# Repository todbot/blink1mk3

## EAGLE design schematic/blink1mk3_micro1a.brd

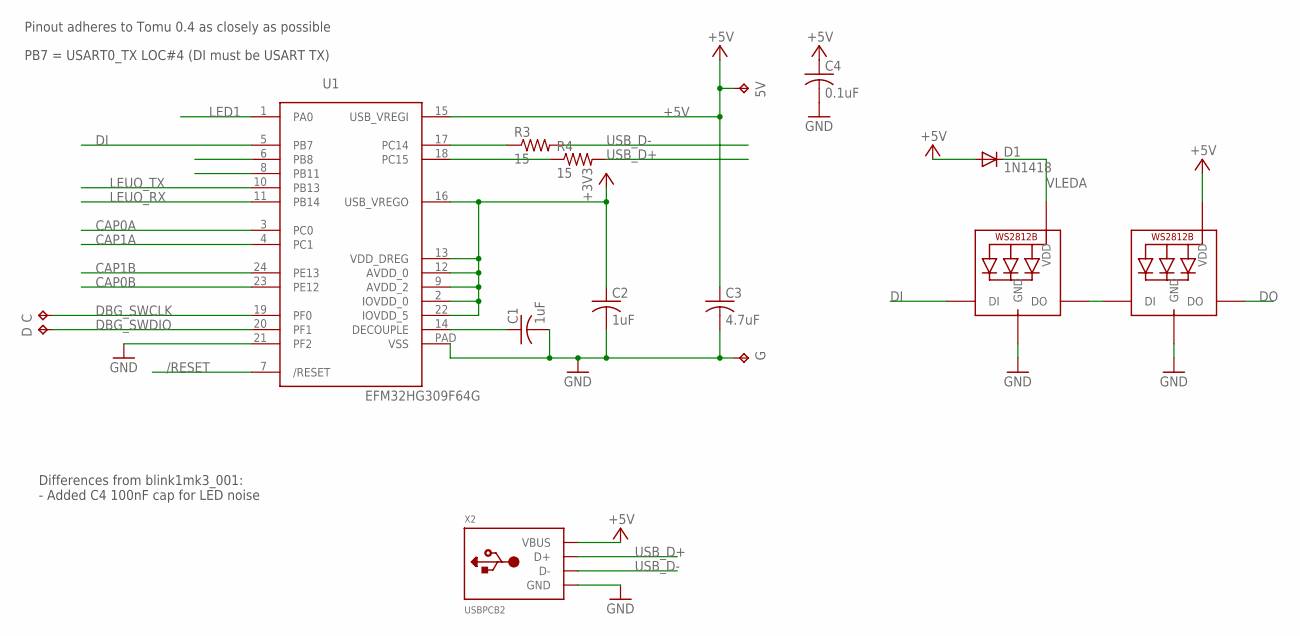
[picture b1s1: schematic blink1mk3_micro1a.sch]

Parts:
5V: TPTP10R; TP10R
C: TPTP10R; TP10R
C1, C2: 1uF; C0402
C3: 4.7uF; C0402
C4: 0.1uF; C0402
D: TPTP10R; TP10R
D1: 1N1418; SOD523
G: TPTP10R; TP10R
LED1, LED2: WS2812B4020SIDE; SK6812-SIDE
R3, R4: 15; R0402
U1: EFM32HG309F64G; QFN24PAD
X2: USBPCB2; USB-A-PCB-2

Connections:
+3V3: C2.1, U1.2 (IOVDD_0), U1.9 (AVDD_2), U1.12 (AVDD_0), U1.13 (VDD_DREG), U1.16 (USB_VREGO), U1.22 (IOVDD_5)
+5V: 5V.TP, C3.1, C4.1, D1.A, LED2.1-VDD (VDD), U1.15 (USB_VREGI), X2.5V (VBUS)
/RESET: U1.7 (/RESET)
CAP0A: U1.3 (PC0)
CAP0B: U1.23 (PE12)
CAP1A: U1.4 (PC1)
CAP1B: U1.24 (PE13)
DBG_SWCLK: C.TP, U1.19 (PF0)
DBG_SWDIO: D.TP, U1.20 (PF1)
DECOUPLE: C1.1, U1.14 (DECOUPLE)
DI: LED1.4-DIN (DI), U1.5 (PB7)
DO: LED2.2-DOUT (DO)
GND: C1.2, C2.2, C3.2, C4.2, G.TP, LED1.3-GND (GND), LED2.3-GND (GND), U1.21 (PF2), U1.PAD (VSS), X2.GND
LED1: U1.1 (PA0)
LEUO_RX: U1.11 (PB14)
LEUO_TX: U1.10 (PB13)
unnamed: LED1.2-DOUT (DO), LED2.4-DIN (DI)
RUSB_D+: R4.1, U1.18 (PC15)
RUSB_D-: R3.1, U1.17 (PC14)
USB_D+: R4.2, X2.USB_P (D+)
USB_D-: R3.2, X2.USB_M (D-)
VLEDA: D1.C, LED1.1-VDD (VDD)

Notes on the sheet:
PB7 = USART0_TX LOC#4 (DI must be USART TX)
Pinout adheres to Tomu 0.4 as closely as possible
Differences from blink1mk3_001: - Added C4 100nF cap for LED noise

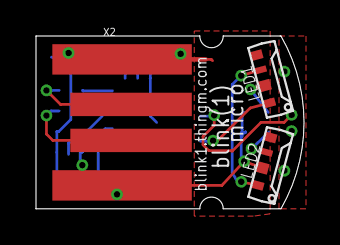
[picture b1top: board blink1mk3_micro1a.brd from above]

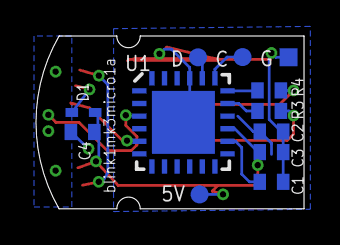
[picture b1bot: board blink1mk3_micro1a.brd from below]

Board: 2 copper layers, 14.9 x 9.6 mm, 15 parts (12 on the bottom side), 13 nets.

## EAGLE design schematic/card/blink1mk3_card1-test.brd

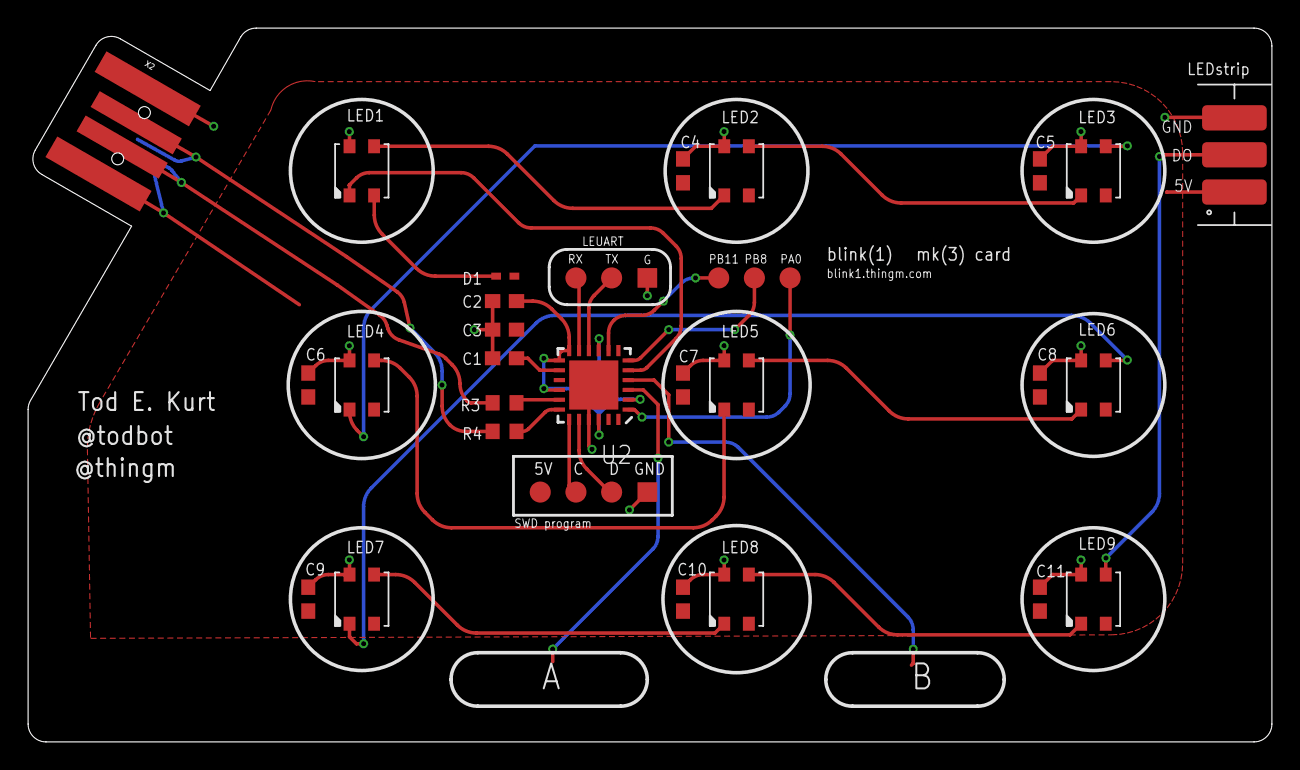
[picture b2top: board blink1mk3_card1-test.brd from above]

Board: 2 copper layers, 88.5 x 50.8 mm, 37 parts (1 on the bottom side), 26 nets.

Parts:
5V: TPTP15R; TP15R
C: TPTP15R; TP15R
C1, C2: 1uF; C0603
C3: 4.7uF; C0603
C4, C5, C6, C7, C8, C9, C10, C11: 0.1uF; C0603
D: TPTP15R; TP15R
D1: 1N1418; SOD523
G: TPTP14SQ; TP14SQ
GND: TPTP14SQ; TP14SQ
J1: NONPOP; USB-B-MICRO-SMD
LED1, LED2, LED3, LED4, LED5, LED6, LED7, LED8, LED9: SK6812MINI; LED3535
PA0: TPTP15R; TP15R
PB8, PB11: TPTP15R; TP15R
R3, R4: 15; R0603
RX: TPTP15R; TP15R
TX: TPTP15R; TP15R
U2: EFM32HG309F64G; QFN24PAD
U$1: LED_STRIP_3P; LEDSTRIP-3P
X2: USBPCB2; USB-A-PCB-2

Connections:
+3V3: C2.1, U2.2, U2.9, U2.12, U2.13, U2.16, U2.22
+5V: 5V.TP, C3.1, C4.1, C5.1, C6.1, C7.1, C8.1, C9.1, C10.1, C11.1, D1.A, J1.VBUS, LED2.2, LED3.2, LED4.2, LED5.2, LED6.2, LED7.2, LED8.2, LED9.2, U2.15, U$1.A, X2.5V
DBG_SWCLK: C.TP, U2.19
DBG_SWDIO: D.TP, U2.20
DECOUPLE: C1.1, U2.14
DI: LED1.1, U2.5
DO: LED9.3, U$1.B
GND: C1.2, C2.2, C3.2, C4.2, C5.2, C6.2, C7.2, C8.2, C9.2, C10.2, C11.2, G.TP, GND.TP, J1.GND, LED1.4, LED2.4, LED3.4, LED4.4, LED5.4, LED6.4, LED7.4, LED8.4, LED9.4, U2.21, U2.PAD, U$1.C, X2.GND
LEUO_RX: RX.TP, U2.11
LEUO_TX: TX.TP, U2.10
unnamed: LED1.3, LED2.1
unnamed: LED7.3, LED8.1
unnamed: LED4.3, LED5.1
unnamed: LED5.3, LED6.1
unnamed: LED2.3, LED3.1
unnamed: LED3.3, LED4.1
unnamed: LED8.3, LED9.1
unnamed: LED6.3, LED7.1
PA0: PA0.TP, U2.1
PB8: PB8.TP, U2.6
PB11: PB11.TP, U2.8
RUSB_D+: R4.1, U2.18
RUSB_D-: R3.1, U2.17
USB_D+: J1.D+, R4.2, X2.USB_P
USB_D-: J1.D-, R3.2, X2.USB_M
VLEDA: D1.C, LED1.2

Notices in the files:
parts and their libraries:
SparkFun-Connectors: Licensing: Creative Commons ShareAlike 4.0 International - https://creativecommons.org/licenses/by-sa/4.0
